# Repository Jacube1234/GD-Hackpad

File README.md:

# GD Hackpad

<br>
View PCB on KiCanvas

<br>
talking about design
<br>
<br>

<br>
video demo
<br>
<br>
<br>

<p align="center">
  <!-- Tall Photos Row -->

</p>
<p align="center">
  <!-- Wide Photos Row -->

</p>
<br>

**Note on images and files:** The photos and physical build shown below do not have the RGB LEDs or don't have them working due to a footprint error on my design. However, the **updated KiCad and Gerber files in this repository include the corrected LED routing**, so if you fabricate a board using the current files, the LEDs will work fully as designed!

This is my Hackpad designed for the purpose to play Geometry Dash Platformer levels. Basically a DIY Sayo Device but cool yk. 
I chose this project as I am comfortable with Fusion 360, and a chance to learn a new program - Kicad.

## Features:
- Cool 3d printed case
- 2 WS2812B RGB LEDs. Kinda under the keys. I just didn't want it to be too basic. Can also tell me whether its powered on.
- 4 arrow keys to play games
- Rotary encoder

## CAD Model:
Everything fits together using 4 M3 Bolts and heatset inserts. 4 for the case.

It has 3 separate printed pieces. The base which has a tilt, the plate to hold the PCB, and the top shell.

Made in Fusion360.

I added these elevated holes because the shell was 3mm tall, which is shorter than the depth needed for the heatset inserts. Still looks visually fine I reckon.

This also shows how it is assembled. The top plate and angled base sandwhich the plate the holds the switches.

## PCB
Here's my PCB!💀 It was made in KiCad. I added the silkscreen image by using the build in image converter.
I got a skull emoji off google, and placed it on my front silkscreen layer.

Schematic

Layout

PCB

## Firmware Overview
This hackpad uses KMK firmware for everything.

I might change the lights to change colour in the future.

## File structure

There's 4 main folders: CAD, Firmware, PCB, and Production. The CAD folder contains the .step file for the case as a whole. It also contains the 3mf of the same thing, and the fusion f3z. The PCB folder contains .kicad_pcb, .kicad_pro, and .kicad_sch. The Firmware folder contains files for KMK firmware. The production folder has files for 3D printing and for the PCB printing.

## BOM (Bill of Materials):
Here should be everything you need to make this hackpad

- 1 Unsoldered Seeed XIAO RP2040
- 4x MX-Style switches
- 4x white blank DSA keycaps
- 2x SK6812 MINI-E LEDs (Neopixels)
- 1x EC11E Rotary Encoder
- 4x M3x16mm screws
- 4x M3x5mx4mm heatset inserts
- 3D printed case
- 3D printed knob
- PCB

## Software

- KMK folder from [here](https://github.com/KMKfw/kmk_firmware/blob/main/docs/en/Getting_Started.md) and have a quick read through. Download where it says "copy of KMK" or [here](https://github.com/KMKfw/kmk_firmware/archive/refs/heads/main.zip)
- UF2 Circuit python [for the Seeed XIAO RP2040](https://circuitpython.org/board/seeeduino_xiao_rp2040/)
- Fusion is recommended if you want to look through my building timeline [here](https://github.com/Jacube1234/GD-Hackpad/blob/main/CAD/Final/Hackpad.f3z)
- Kicad recommended to view the Gerber files or the general `.pcb` `.pro` `.sch` files
## Tools:

- 3D Printer
- Soldering Iron
- Solder
- M3 Allen key

## How to build/replicate
1. Get **everything** that is on the BOM.

- Download the step files from [here](https://github.com/Jacube1234/GD-Hackpad/tree/main/Production) and 3d print them.
- Use the Gerber files [here](https://github.com/Jacube1234/GD-Hackpad/tree/main/Production) to order the pcb online.
- Buy the screws and heatset inserts online or at a hardware store.
- Buy the rest of the items online somewhere (sorry!)

Note that I will be getting most parts from Alex's Hackpad kit, and and the pcb ordered with the $15 grant.

2. **Solder** the parts **but *NOT* the switches** in their specificed location using solder and a soldering iron.
- If you need help refer to the images earlier in this `README.md` or [here](https://github.com/Jacube1234/GD-Hackpad/tree/main/assets)

3. **Install the heat-set inserts.** Heat up your soldering iron and gently press the 4 M3 heat-set inserts into the 3D printed case. Take your time and let the heat do the work so you don't accidentally melt all the way through the plastic.

4. **Put the software on the XIAO RP2040.** Plug the microcontroller into your computer and drop the CircuitPython `.uf2` file from [here](https://circuitpython.org/board/seeeduino_xiao_rp2040/) onto the `RPI-RP2` drive. Basically follow [this](https://github.com/KMKfw/kmk_firmware/blob/main/docs/en/Getting_Started.md)

5. **Install KMK and your code.** Put the `kmk` folder from the KMK firmware zip and the files from the `Firmware` folder in this repository onto the new `CIRCUITPY` drive.

6. **Assemble the hardware.** Snap your 4 MX switches through the 3D-printed plate so they sit securely. Sandwich your finished PCB between the base piece and the top shell, making sure the plate is aligned correctly. 

7. **Screw it together.** Thread your 4 M3x16mm screws through the bottom of the case and into the heat-set inserts you installed in step 3. Try not to overtighten them.

8. **Finishing touches.** Slap your 4 blank white DSA keycaps onto the switches and push the custom 3D-printed knob onto the rotary encoder.

Hopefully it should work flawlessly because I have 100% tested the code.

## Project Reflection
Some stuff already mentioned elsewhere in this `README.md`
- **What I made:** I made the GD Hackpad—a custom 4-key macro pad with a rotary encoder designed specifically for playing Geometry Dash Platformer levels (basically a DIY Sayo Device). It features a 3-piece 3D-printed angled case designed in Fusion 360, a custom PCB featuring a skull silkscreen created in KiCad, and is powered by a Seeed XIAO RP2040 running KMK firmware.
- **What was challenging:** Learning KiCad from scratch since I was originally much more comfortable with Fusion 360. Learning the stardance process and this general hackclub stuff.
- **What I am proud of:** How well the 3D-printed case fits together using M3 bolts and heat-set inserts, adding a custom skull emoji silkscreen to the PCB, and getting everything running smoothly with 100% tested code.
- **How to test:** Everything you need to replicate it is in the repository, including the 3D print production files, Gerber files for ordering the PCB, the BOM, and a full guide on setting up CircuitPython and KMK firmware. Note: The photos of my physical build ldon’t have the RGB LEDs due to an early board error, but the updated KiCad and Gerber files in the repo feature the corrected LED routing!

## Extra stuff
Hi guys

Bye guys

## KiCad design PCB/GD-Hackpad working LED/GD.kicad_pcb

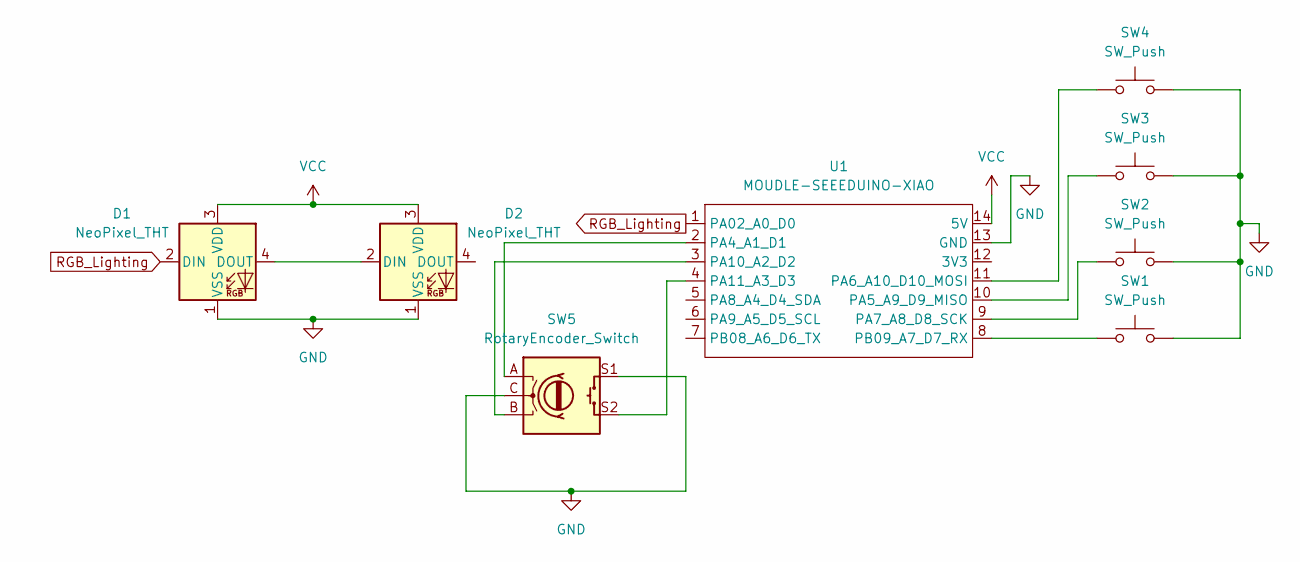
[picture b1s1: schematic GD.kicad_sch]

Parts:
D1, D2: NeoPixel_THT; LED_SK6812MINI-E_3.2x2.8mm_P1.5mm_ReverseMount
SW1, SW2, SW3, SW4: SW_Push; SW_Cherry_MX_1.00u_PCB
SW5: RotaryEncoder_Switch; RotaryEncoder_Alps_EC11E-Switch_Vertical_H20mm
U1: MOUDLE-SEEEDUINO-XIAO; XIAO-Generic-Hybrid-14P-2.54-21X17.8MM

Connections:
GND: D1.1 (VSS), D2.1 (VSS), SW1.2, SW2.2, SW3.2, SW4.2, SW5.C, SW5.S1, U1.13 (GND)
unnamed: D1.4 (DOUT), D2.2 (DIN)
unnamed: SW5.A, U1.2 (PA4_A1_D1)
unnamed: SW3.1, U1.10 (PA5_A9_D9_MISO)
unnamed: SW4.1, U1.11 (PA6_A10_D10_MOSI)
unnamed: SW2.1, U1.9 (PA7_A8_D8_SCK)
unnamed: SW5.B, U1.3 (PA10_A2_D2)
unnamed: SW5.S2, U1.4 (PA11_A3_D3)
unnamed: SW1.1, U1.8 (PB09_A7_D7_RX)
RGB_Lighting: D1.2 (DIN), U1.1 (PA02_A0_D0)
VCC: D1.3 (VDD), D2.3 (VDD), U1.14 (5V)

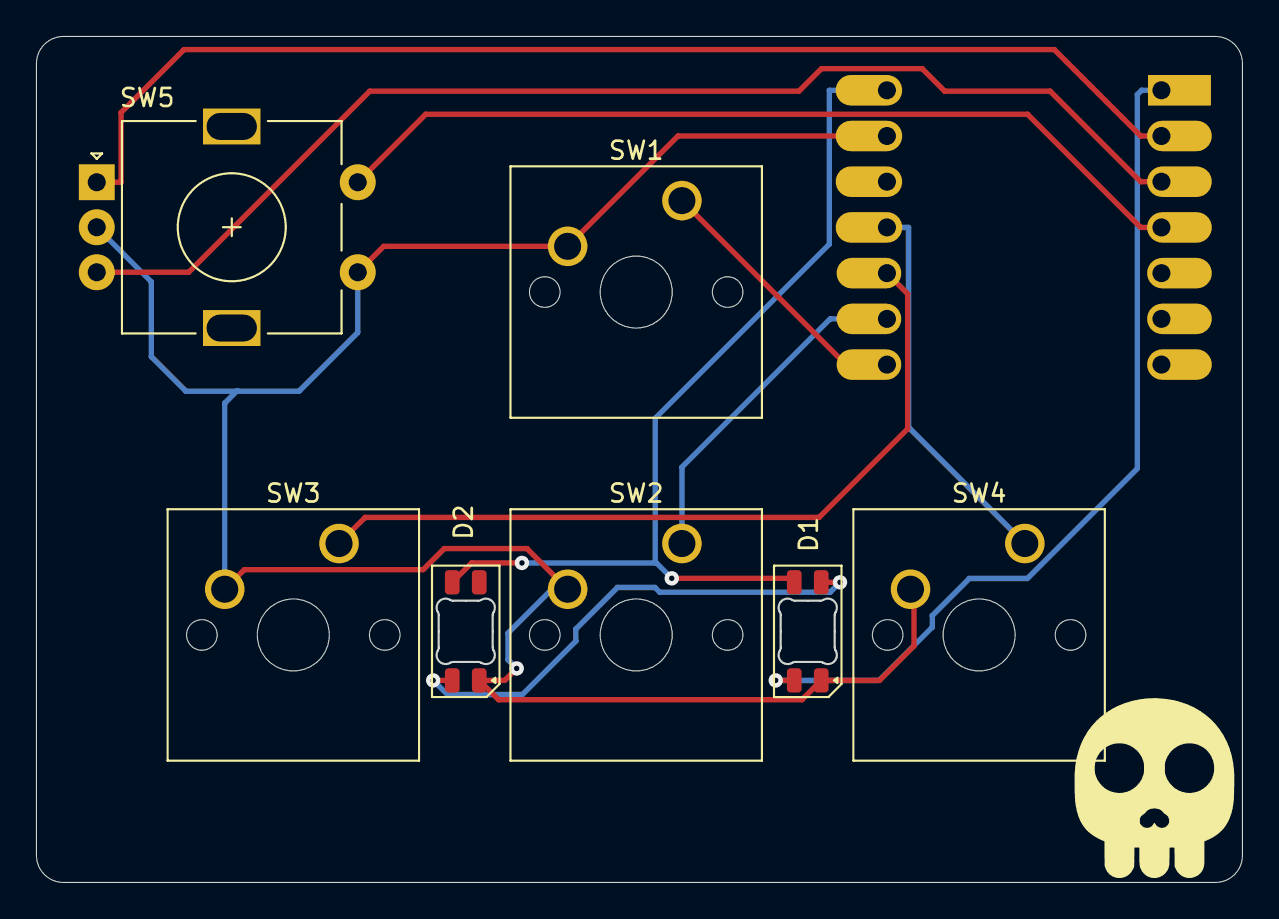
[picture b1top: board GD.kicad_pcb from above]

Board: 2 copper layers, 67.0 x 47.0 mm, 8 parts (1 on the bottom side), 11 nets.
